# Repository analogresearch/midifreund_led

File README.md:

# midifreund_led

DC IN: 9..28 V 

Ansteuerung durch MIDI note 36 (C2) und eine Oktave dur hoch bis C3.
also:
36 38 40 41 43 45 47 48

MIDI channel und Programm werden binär über DIP Schalter gewählt.

MIDI: Ausnahme DIP Schalter 0000 = MIDI channel 16!

programme:  
0 triggert durch note on einen kurzen 100% Blitz der auf 0 ausfaded.  
1 triggert durch note on einen kurzen Blitz mit Starthelligkeit velocity der dann auf 0 ausfaded.  
2 note on schaltet Led mit Helligkeit velocity ein. Helligkeit kann dann mit aftertouch poly moduliert werden. note off schaltet Led aus.

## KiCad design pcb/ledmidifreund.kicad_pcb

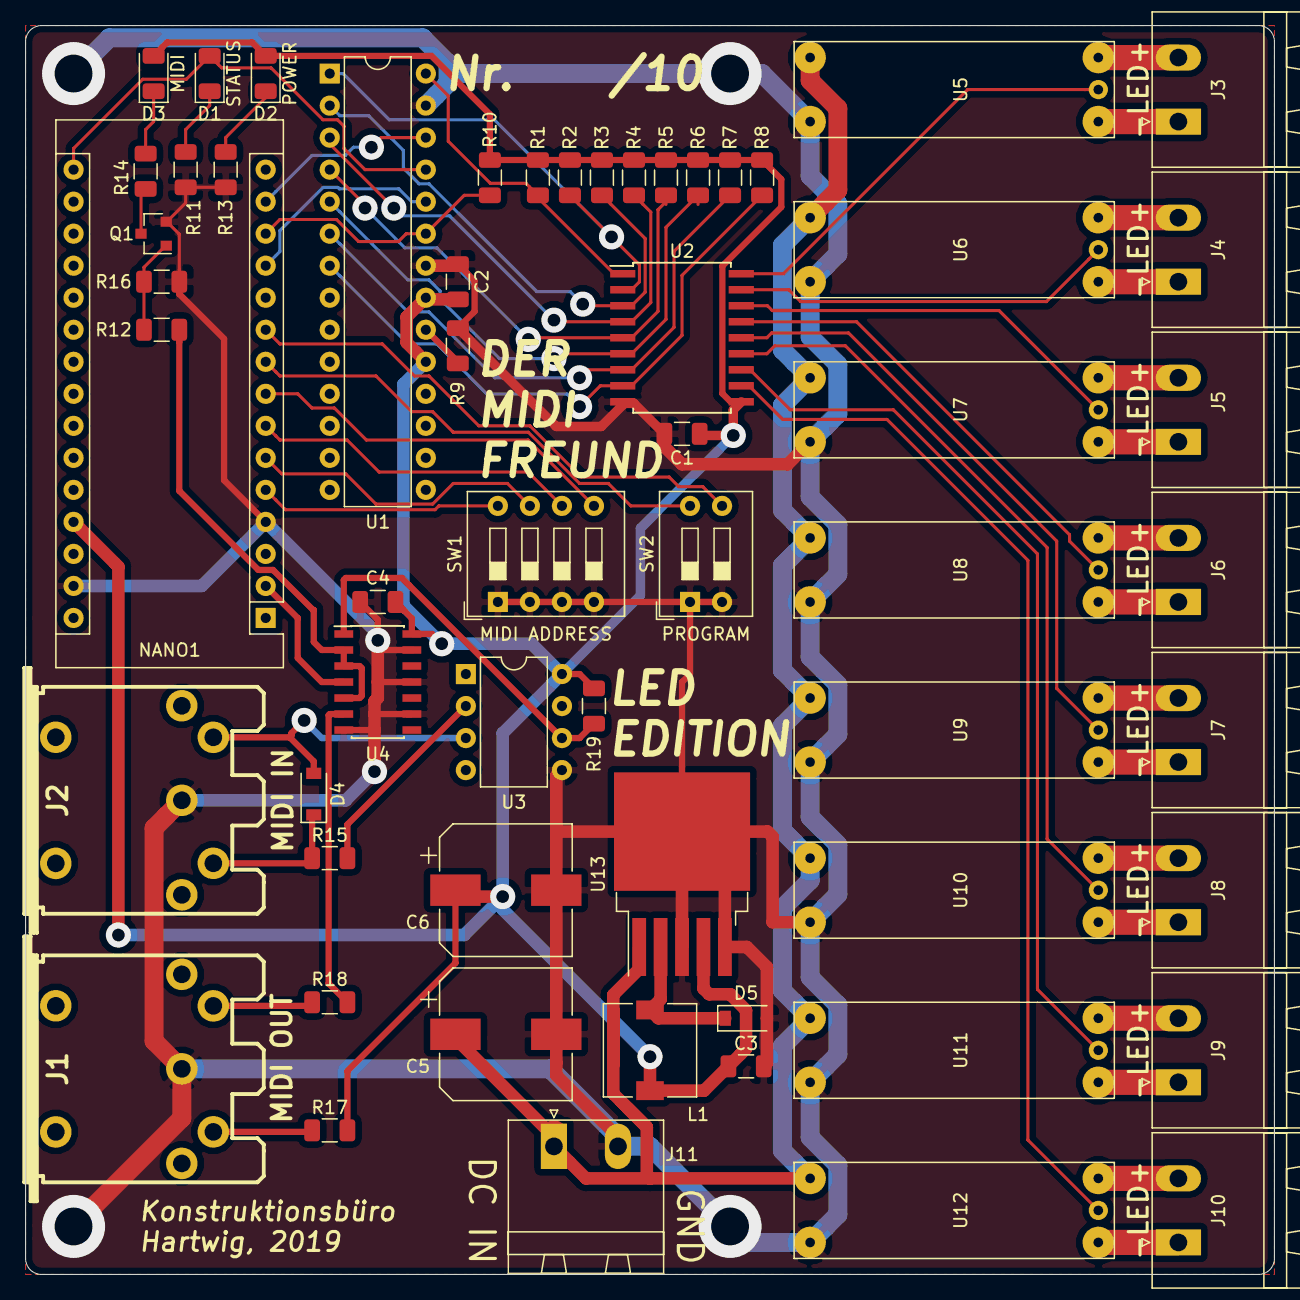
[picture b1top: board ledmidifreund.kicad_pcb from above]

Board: 2 copper layers, 99.1 x 99.1 mm, 59 parts (0 on the bottom side), 61 nets.

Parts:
C1, C2, C3, C4: 100n; C_1206_3216Metric
C5, C6: 330uF; CP_Elec_10x10
D1: STATUS; LED_1206_3216Metric
D2: POWER; LED_1206_3216Metric
D3: MIDI; LED_1206_3216Metric
D4: 1N4148; D_SOD-123
D5: 1N5819; D_SOD-123
J1: MIDI OUT; MIDI_DIN5
J2: MIDI IN; MIDI_DIN5
J3, J4, J5, J6, J7, J8, J9, J10, J11: Conn_01x02; PhoenixContact_MSTBA_2,5_2-G-5,08_1x02_P5.08mm_Horizontal
L1: 330uH; L_7.3x7.3_H3.5
NANO1: Arduino_Nano_v3.x; Arduino_Nano
Q1: BSS138; SOT-23
R1, R2, R3, R4, R5, R6, R7, R8, R12: 1k; R_1206_3216Metric
R9: 2k2; R_1206_3216Metric
R10: 10k; R_1206_3216Metric
R11: 470; R_1206_3216Metric
R13, R14, R15, R17, R18: 220; R_1206_3216Metric
R16: 47k; R_1206_3216Metric
R19: 280; R_1206_3216Metric
SW1: SW_DIP_x04; SW_DIP_SPSTx04_Slide_9.78x12.34mm_W7.62mm_P2.54mm
SW2: SW_DIP_x02; SW_DIP_SPSTx02_Slide_9.78x7.26mm_W7.62mm_P2.54mm
U1: TLC5940NT; DIP-28_W7.62mm
U2: ULN2803A; SOIC-18W_7.5x11.6mm_P1.27mm
U3: 6N137; DIP-8_W7.62mm
U4: 74LS14; SOIC-14_3.9x8.7mm_P1.27mm
U5, U6, U7, U8, U9, U10, U11, U12: LEDREG1
U13: LM2575-5.0BU; TO-263-5_TabPin3

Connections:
+5V: C1.1, C2.1, C3.1, C4.1, C6.1, D2.2, D3.2, L1.2, NANO1.27, R1.1, R2.1, R3.1, R4.1, R5.1, R6.1, R7.1, R8.1, R10.2, R17.2, R19.1, U1.19, U1.21, U2.10, U3.8, U4.14, U13.4
GND: C1.2, C2.2, C3.2, C4.2, C5.2, C6.2, D5.2, J1.2, J2.2, J11.2, NANO1.4, NANO1.29, Q1.2, R9.2, R11.2, R13.1, R16.2, SW1.1, SW1.2, SW1.3, SW1.4, SW2.1, SW2.2, U1.22, U1.27, U2.9, U3.5, U4.7, U4.9, U4.11, U4.13, U5.3, U6.3, U7.3, U8.3, U9.3, U10.3, U11.3, U12.3, U13.3, U13.5
unnamed: D1.1, R11.1
unnamed: D1.2, NANO1.16, U1.25
unnamed: D2.1, R13.2
unnamed: D3.1, R14.1
unnamed: D4.1, J2.4, R15.1
unnamed: D4.2, J2.5, U3.3
unnamed: D5.1, L1.1, U13.2
unnamed: J1.4, R17.1
unnamed: J1.5, R18.1
unnamed: J3.1, U5.4
unnamed: J3.2, U5.1
unnamed: J4.1, U6.4
unnamed: J4.2, U6.1
unnamed: J5.1, U7.4
unnamed: J5.2, U7.1
unnamed: J6.1, U8.4
unnamed: J6.2, U8.1
unnamed: J7.1, U9.4
unnamed: J7.2, U9.1
unnamed: J8.1, U10.4
unnamed: J8.2, U10.1
unnamed: J9.1, U11.4
unnamed: J9.2, U11.1
unnamed: J10.1, U12.4
unnamed: J10.2, U12.1
unnamed: NANO1.2, U4.4
unnamed: NANO1.5, SW1.8
unnamed: NANO1.6, SW1.7
unnamed: NANO1.7, SW1.6
unnamed: NANO1.8, SW1.5
unnamed: NANO1.9, SW2.4
unnamed: NANO1.10, SW2.3
unnamed: NANO1.12, U1.24
unnamed: NANO1.13, R10.1, U1.23
unnamed: NANO1.14, U1.26
unnamed: Q1.1, R12.2, R16.1
unnamed: Q1.3, R14.2
unnamed: R1.2, U1.28, U2.1
unnamed: R2.2, U1.1, U2.2
unnamed: R3.2, U1.2, U2.3
unnamed: R4.2, U1.3, U2.4
unnamed: R5.2, U1.4, U2.5
unnamed: R6.2, U1.5, U2.6
unnamed: R7.2, U1.6, U2.7
unnamed: R8.2, U1.7, U2.8
unnamed: R9.1, U1.20
unnamed: R12.1, U4.2, U4.3, U4.5
unnamed: R15.2, U3.2
unnamed: R18.2, U4.6
unnamed: R19.2, U3.6, U4.1
unnamed: U2.14, U9.5
unnamed: U2.15, U8.5
unnamed: U2.16, U7.5
unnamed: U2.17, U6.5
unnamed: U2.18, U5.5
unnamed: U2.13, U10.5
unnamed: U2.12, U11.5
unnamed: U2.11, U12.5
VDD: C5.1, J11.1, U5.2, U6.2, U7.2, U8.2, U9.2, U10.2, U11.2, U12.2, U13.1

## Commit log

2019-05-08 .svg ending
2019-05-08 foto hinzugefügt
2020-12-02 added pcb layout
